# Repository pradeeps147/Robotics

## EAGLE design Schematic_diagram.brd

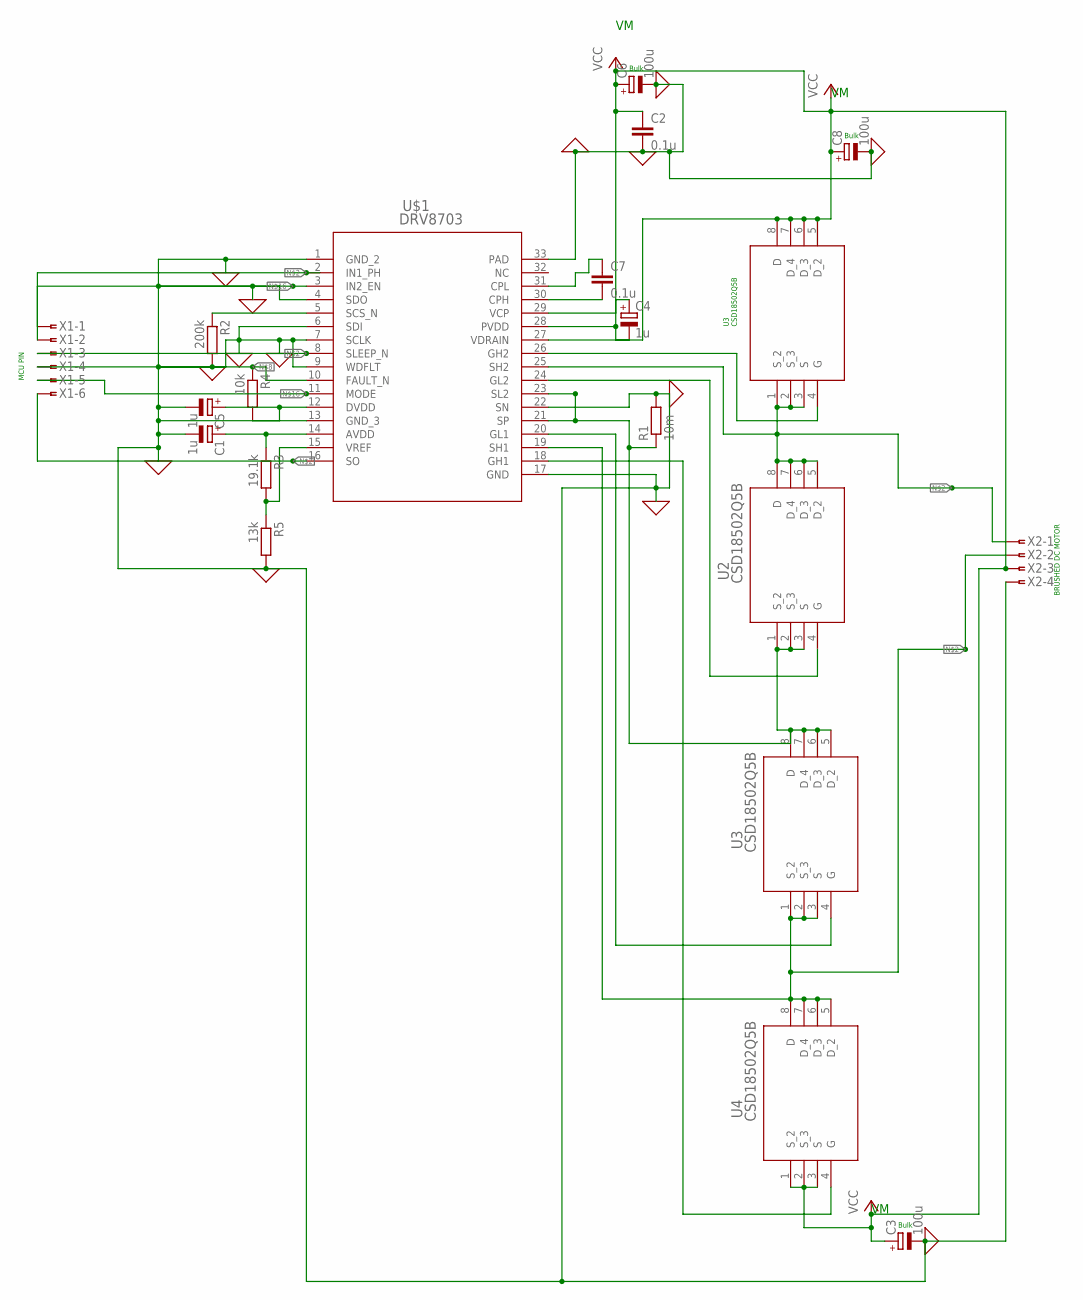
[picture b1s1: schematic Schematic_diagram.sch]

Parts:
C1, C4, C5: 1u; E5-5
C2, C7: 0.1u; C0805K
C3, C6, C8: 100u; E5-10,5
R1: 10m; 0207/7
R2: 200k; 0207/7
R3: 19.1k; 0207/7
R4: 10k; 0207/7
R5: 13k; 0207/7
U1, U2, U3, U4: CSD18502Q5B; DNK8
U$1: DRV8703; RHB0032E
X1: FTOP-6
X2: FTOP-4

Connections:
0: C1.-, C2.2, C3.-, C5.+, C5.-, C6.-, C8.-, R1.1, R1.2, R2.2, R4.2, R5.2, U2.1 (S_2), U2.2 (S_3), U2.3 (S), U3.5 (D_2), U3.6 (D_3), U3.7 (D_4), U3.8 (D), U$1.1 (GND_2), U$1.4 (SDO), U$1.6 (SDI), U$1.7 (SCLK), U$1.9 (WDFLT), U$1.12 (DVDD), U$1.13 (GND_3), U$1.17 (GND), U$1.21 (SP), U$1.22 (SN), U$1.23 (SL2), U$1.33 (PAD), X2.4
unnamed: U1.1 (S_2), U1.2 (S_3), U1.3 (S), U2.5 (D_2), U2.6 (D_3), U2.7 (D_4), U2.8 (D), U$1.25 (SH2), X2.1
unnamed: U$1.2 (IN1_PH), X1.1
unnamed: U4.4 (G), U$1.18 (GH1)
unnamed: U3.1 (S_2), U3.2 (S_3), U3.3 (S), U4.5 (D_2), U4.6 (D_3), U4.7 (D_4), U4.8 (D), U$1.19 (SH1), X2.2
unnamed: U3.4 (G), U$1.20 (GL1)
unnamed: R2.1, U$1.5 (SCS_N)
unnamed: U2.4 (G), U$1.24 (GL2)
unnamed: R4.1, U$1.10 (FAULT_N), X1.4
unnamed: U1.4 (G), U$1.26 (GH2)
unnamed: R3.2, R5.1, U$1.15 (VREF)
unnamed: C1.+, R3.1, U$1.14 (AVDD)
unnamed: C7.1, U$1.31 (CPL)
unnamed: C7.2, U$1.30 (CPH)
unnamed: C4.+, U$1.29 (VCP)
unnamed: U$1.3 (IN2_EN), X1.2
unnamed: U$1.8 (SLEEP_N), X1.3
unnamed: U$1.16 (SO), X1.6
unnamed: U$1.11 (MODE), X1.5
VCC: C2.1, C3.+, C4.-, C6.+, C8.+, U1.5 (D_2), U1.6 (D_3), U1.7 (D_4), U1.8 (D), U4.1 (S_2), U4.2 (S_3), U4.3 (S), U$1.27 (VDRAIN), U$1.28 (PVDD), X2.3

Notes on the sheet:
BRUSHED DC MOTOR
Bulk
U3 CSD18502Q5B
MCU PIN

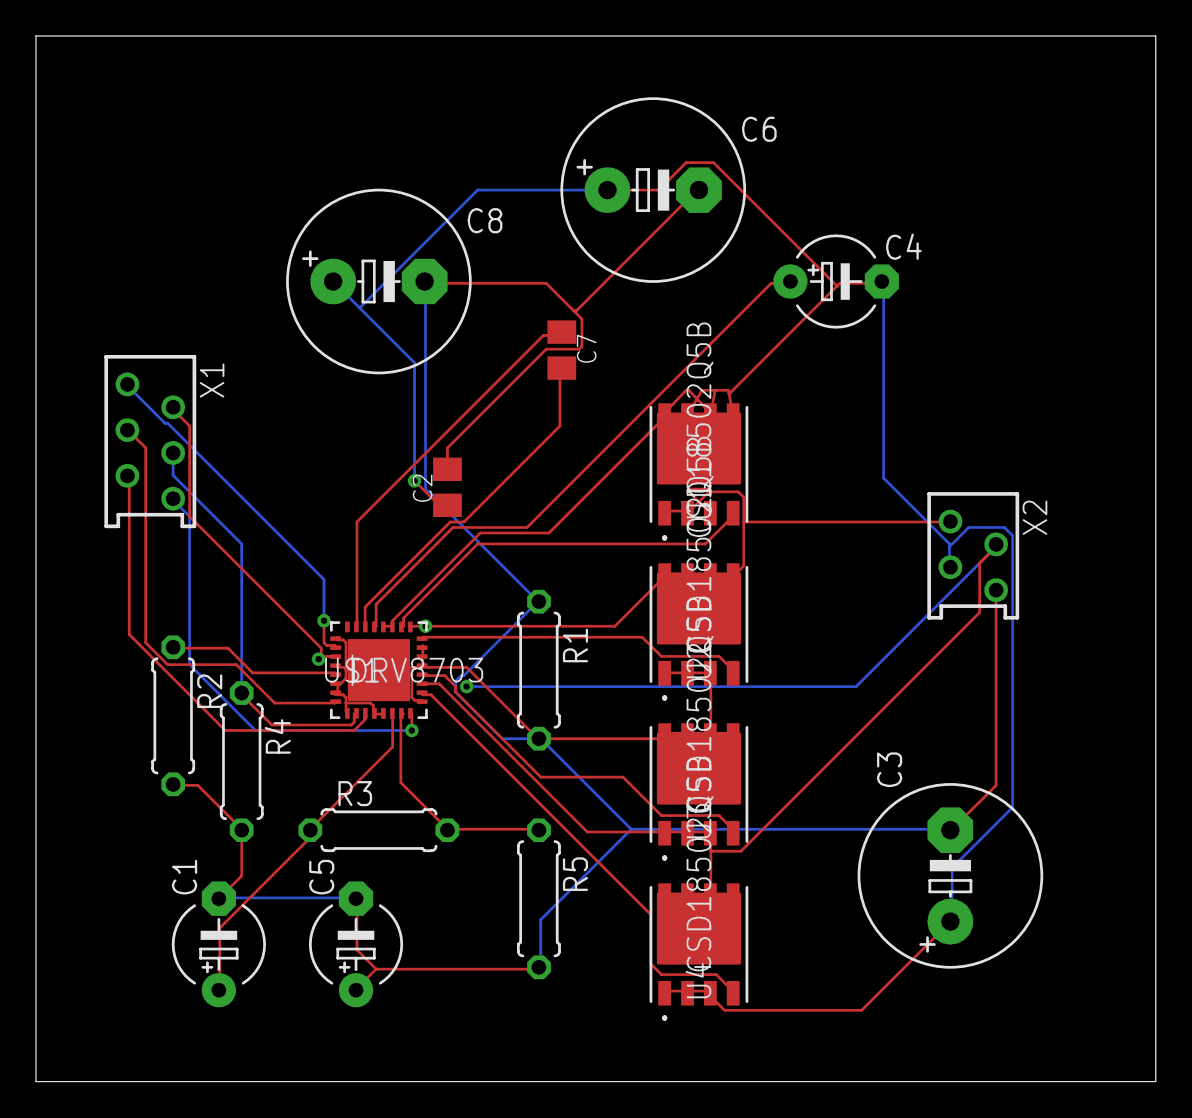
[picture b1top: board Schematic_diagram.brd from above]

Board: 2 copper layers, 62.2 x 58.1 mm, 20 parts (0 on the bottom side), 20 nets.

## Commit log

2020-02-08 Create stepper motor control
